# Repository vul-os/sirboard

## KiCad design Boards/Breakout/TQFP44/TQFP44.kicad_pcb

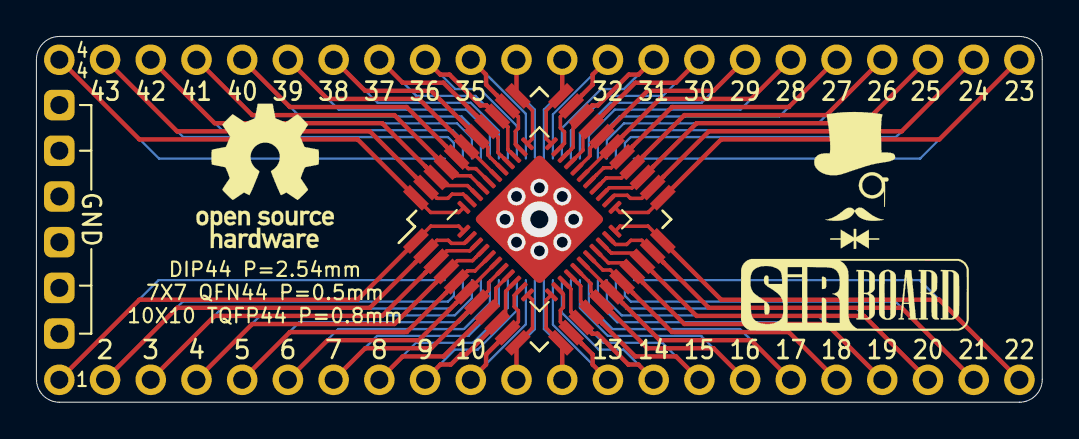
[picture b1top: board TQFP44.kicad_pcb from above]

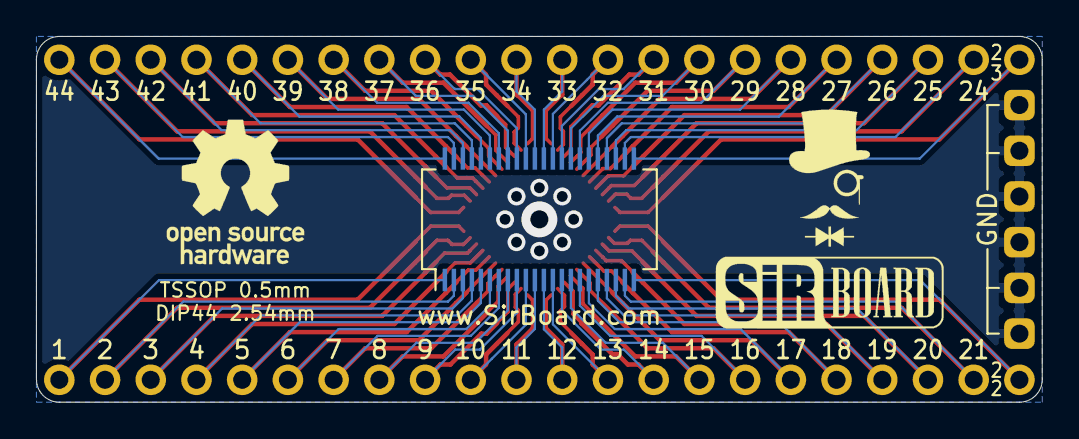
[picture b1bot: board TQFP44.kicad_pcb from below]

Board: 2 copper layers, 55.9 x 20.3 mm, 6 parts (2 on the bottom side), 45 nets.

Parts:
J1, J2: Conn_01x22; PinHeader_1x22_P2.54mm_Vertical
J3: Conn_02x22_Counter_Clockwise; TQFP-44_10x10mm_P0.8mm
J4: Conn_02x22_Counter_Clockwise; QFN-44-1EP_7x7mm_P0.5mm_EP5.15x5.15mm
J5: Conn_02x22_Counter_Clockwise; SSOP-44_5.3x12.8mm_P0.5mm
J6: Conn_01x06; PinHeader_1x06_P2.54mm_Vertical

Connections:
unnamed: J1.1, J3.44, J4.44, J5.23
unnamed: J1.2, J3.43, J4.43, J5.24
unnamed: J1.3, J3.42, J4.42, J5.25
unnamed: J1.4, J3.41, J4.41, J5.26
unnamed: J1.5, J3.40, J4.40, J5.27
unnamed: J1.6, J3.39, J4.39, J5.28
unnamed: J1.7, J3.38, J4.38, J5.29
unnamed: J1.8, J3.37, J4.37, J5.30
unnamed: J1.9, J3.36, J4.36, J5.31
unnamed: J1.10, J3.35, J4.35, J5.32
unnamed: J1.11, J3.34, J4.34, J5.33
unnamed: J1.12, J3.33, J4.33, J5.34
unnamed: J1.13, J3.32, J4.32, J5.35
unnamed: J1.14, J3.31, J4.31, J5.36
unnamed: J1.15, J3.30, J4.30, J5.37
unnamed: J1.16, J3.29, J4.29, J5.38
unnamed: J1.17, J3.28, J4.28, J5.39
unnamed: J1.18, J3.27, J4.27, J5.40
unnamed: J1.19, J3.26, J4.26, J5.41
unnamed: J1.20, J3.25, J4.25, J5.42
unnamed: J1.21, J3.24, J4.24, J5.43
unnamed: J1.22, J3.23, J4.23, J5.44
unnamed: J2.1, J3.1, J4.1, J5.22
unnamed: J2.2, J3.2, J4.2, J5.21
unnamed: J2.3, J3.3, J4.3, J5.20
unnamed: J2.4, J3.4, J4.4, J5.19
unnamed: J2.5, J3.5, J4.5, J5.18
unnamed: J2.6, J3.6, J4.6, J5.17
unnamed: J2.7, J3.7, J4.7, J5.16
unnamed: J2.8, J3.8, J4.8, J5.15
unnamed: J2.9, J3.9, J4.9, J5.14
unnamed: J2.10, J3.10, J4.10, J5.13
unnamed: J2.11, J3.11, J4.11, J5.12
unnamed: J2.12, J3.12, J4.12, J5.11
unnamed: J2.13, J3.13, J4.13, J5.10
unnamed: J2.14, J3.14, J4.14, J5.9
unnamed: J2.15, J3.15, J4.15, J5.8
unnamed: J2.16, J3.16, J4.16, J5.7
unnamed: J2.17, J3.17, J4.17, J5.6
unnamed: J2.18, J3.18, J4.18, J5.5
unnamed: J2.19, J3.19, J4.19, J5.4
unnamed: J2.20, J3.20, J4.20, J5.3
unnamed: J2.21, J3.21, J4.21, J5.2
unnamed: J2.22, J3.22, J4.22, J5.1
unnamed: J4.45, J6.1, J6.2, J6.3, J6.4, J6.5, J6.6

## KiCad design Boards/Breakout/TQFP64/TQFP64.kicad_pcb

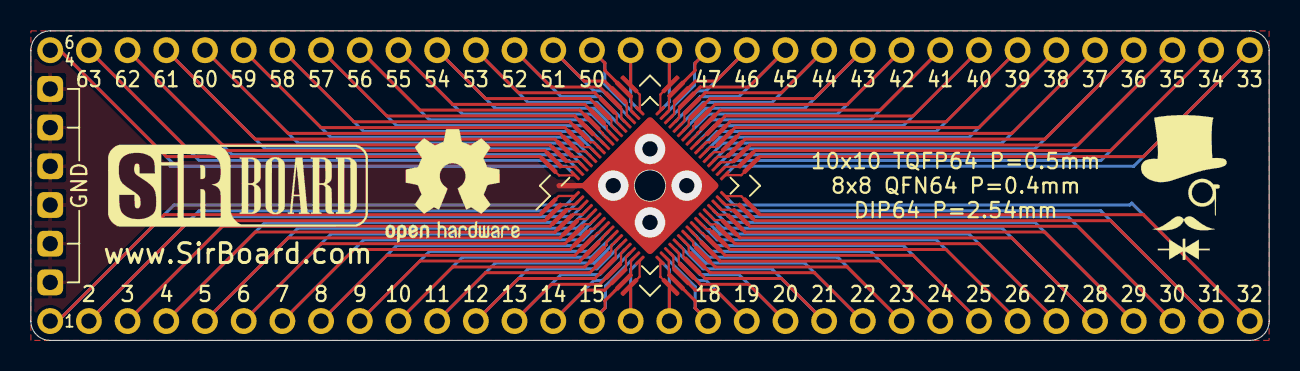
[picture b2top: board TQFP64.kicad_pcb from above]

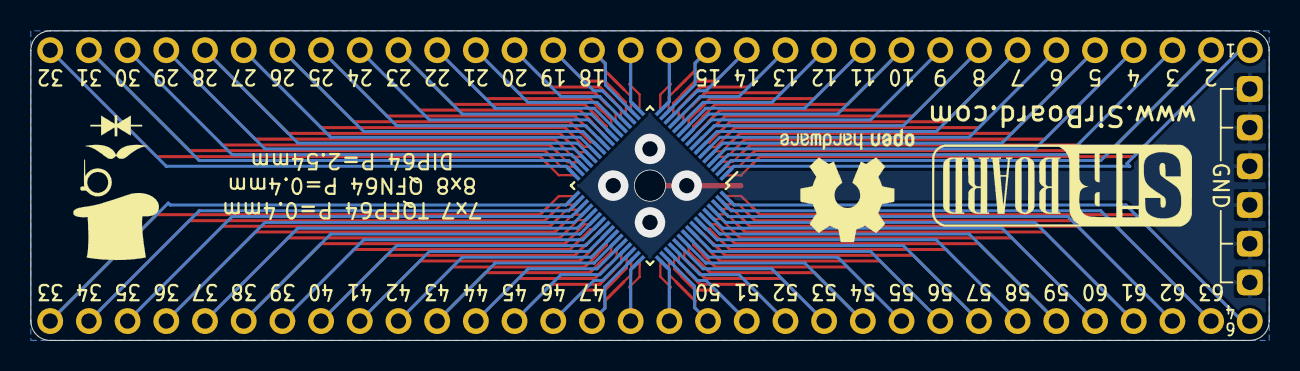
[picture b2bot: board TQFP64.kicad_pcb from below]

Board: 2 copper layers, 81.3 x 20.3 mm, 6 parts (4 on the bottom side), 65 nets.

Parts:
J1, J5: Conn_01x32; PinHeader_1x32_P2.54mm_Vertical
J2: Conn_02x32_Counter_Clockwise; TQFP-64_10x10mm_P0.5mm
J3: Conn_02x32_Counter_Clockwise; QFN-64-1EP_8x8mm_P0.4mm_EP6.5x6.5mm
J4: Conn_02x32_Counter_Clockwise; TQFP-64_7x7mm_P0.4mm
J6: Conn_01x06; PinHeader_1x06_P2.54mm_Vertical

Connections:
unnamed: J1.1, J2.1, J3.1, J4.64
unnamed: J1.2, J2.2, J3.2, J4.63
unnamed: J1.3, J2.3, J3.3, J4.62
unnamed: J1.4, J2.4, J3.4, J4.61
unnamed: J1.5, J2.5, J3.5, J4.60
unnamed: J1.6, J2.6, J3.6, J4.59
unnamed: J1.7, J2.7, J3.7, J4.58
unnamed: J1.8, J2.8, J3.8, J4.57
unnamed: J1.9, J2.9, J3.9, J4.56
unnamed: J1.10, J2.10, J3.10, J4.55
unnamed: J1.11, J2.11, J3.11, J4.54
unnamed: J1.12, J2.12, J3.12, J4.53
unnamed: J1.13, J2.13, J3.13, J4.52
unnamed: J1.14, J2.14, J3.14, J4.51
unnamed: J1.15, J2.15, J3.15, J4.50
unnamed: J1.16, J2.16, J3.16, J4.49
unnamed: J1.17, J2.17, J3.17, J4.48
unnamed: J1.18, J2.18, J3.18, J4.47
unnamed: J1.19, J2.19, J3.19, J4.46
unnamed: J1.20, J2.20, J3.20, J4.45
unnamed: J1.21, J2.21, J3.21, J4.44
unnamed: J1.22, J2.22, J3.22, J4.43
unnamed: J1.23, J2.23, J3.23, J4.42
unnamed: J1.24, J2.24, J3.24, J4.41
unnamed: J1.25, J2.25, J3.25, J4.40
unnamed: J1.26, J2.26, J3.26, J4.39
unnamed: J1.27, J2.27, J3.27, J4.38
unnamed: J1.28, J2.28, J3.28, J4.37
unnamed: J1.29, J2.29, J3.29, J4.36
unnamed: J1.30, J2.30, J3.30, J4.35
unnamed: J1.31, J2.31, J3.31, J4.34
unnamed: J1.32, J2.32, J3.32, J4.33
unnamed: J2.33, J3.33, J4.32, J5.32
unnamed: J2.34, J3.34, J4.31, J5.31
unnamed: J2.35, J3.35, J4.30, J5.30
unnamed: J2.36, J3.36, J4.29, J5.29
unnamed: J2.37, J3.37, J4.28, J5.28
unnamed: J2.38, J3.38, J4.27, J5.27
unnamed: J2.39, J3.39, J4.26, J5.26
unnamed: J2.40, J3.40, J4.25, J5.25
unnamed: J2.41, J3.41, J4.24, J5.24
unnamed: J2.42, J3.42, J4.23, J5.23
unnamed: J2.43, J3.43, J4.22, J5.22
unnamed: J2.44, J3.44, J4.21, J5.21
unnamed: J2.45, J3.45, J4.20, J5.20
unnamed: J2.46, J3.46, J4.19, J5.19
unnamed: J2.47, J3.47, J4.18, J5.18
unnamed: J2.48, J3.48, J4.17, J5.17
unnamed: J2.49, J3.49, J4.16, J5.16
unnamed: J2.50, J3.50, J4.15, J5.15
unnamed: J2.51, J3.51, J4.14, J5.14
unnamed: J2.52, J3.52, J4.13, J5.13
unnamed: J2.53, J3.53, J4.12, J5.12
unnamed: J2.54, J3.54, J4.11, J5.11
unnamed: J2.55, J3.55, J4.10, J5.10
unnamed: J2.56, J3.56, J4.9, J5.9
unnamed: J2.57, J3.57, J4.8, J5.8
unnamed: J2.58, J3.58, J4.7, J5.7
unnamed: J2.59, J3.59, J4.6, J5.6
unnamed: J2.60, J3.60, J4.5, J5.5
unnamed: J2.61, J3.61, J4.4, J5.4
unnamed: J2.62, J3.62, J4.3, J5.3
unnamed: J2.63, J3.63, J4.2, J5.2
unnamed: J2.64, J3.64, J4.1, J5.1
unnamed: J3.65, J6.1, J6.2, J6.3, J6.4, J6.5, J6.6

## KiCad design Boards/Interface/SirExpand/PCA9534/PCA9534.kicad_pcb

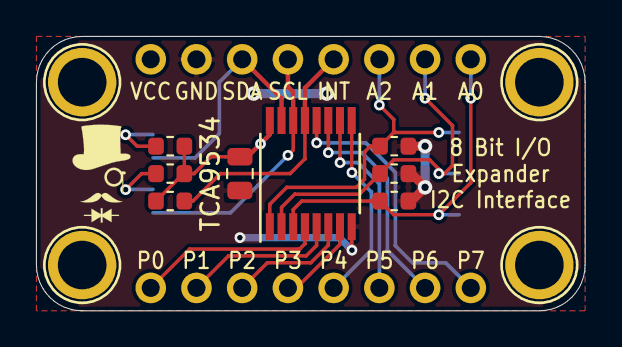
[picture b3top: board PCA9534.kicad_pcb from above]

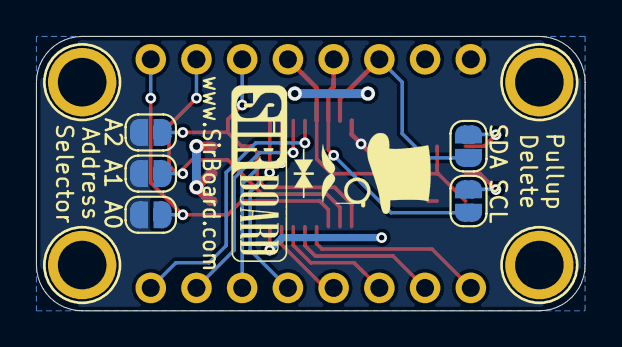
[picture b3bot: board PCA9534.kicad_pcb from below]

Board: 2 copper layers, 30.5 x 15.2 mm, 19 parts (5 on the bottom side), 18 nets.

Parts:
A0, A1, A2: SolderJumper_2_Open; SolderJumper-2_P1.3mm_Open_RoundedPad1.0x1.5mm
C1: 10uF; C_0805_2012Metric
H1, H2, H3, H4: MountingHole; MountingHole_M2.5_SirBoard
J1, J2: Conn_01x08; PinHeader_1x08_P2.54mm_Vertical
R1, R2, R3, R4, R5, R6: 10K; R_0603_1608Metric
SCL: SolderJumper_2_Open; SolderJumper-2_P1.3mm_Open_RoundedPad1.0x1.5mm
SDA: SolderJumper_2_Open; SolderJumper-2_P1.3mm_Open_RoundedPad1.0x1.5mm
TCA9534: TCA9534; TSSOP-16_4.4x5mm_P0.65mm

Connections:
A0: A0.1, J1.8, R1.1, TCA9534.3
A1: A1.1, J1.7, R4.1, TCA9534.2
A2: A2.1, J1.6, R5.1, TCA9534.1
GND: C1.2, J1.2, R1.2, R4.2, R5.2, TCA9534.8
INT: J1.5, R6.2, TCA9534.13
unnamed: R2.2, SCL.1
unnamed: R3.2, SDA.1
P0: J2.8, TCA9534.4
P1: J2.7, TCA9534.5
P2: J2.6, TCA9534.6
P3: J2.5, TCA9534.7
P4: J2.4, TCA9534.9
P5: J2.3, TCA9534.10
P6: J2.2, TCA9534.11
P7: J2.1, TCA9534.12
SCL: J1.4, SCL.2, TCA9534.14
SDA: J1.3, SDA.2, TCA9534.15
VCC: A0.2, A1.2, A2.2, C1.1, J1.1, R2.1, R3.1, R6.1, TCA9534.16

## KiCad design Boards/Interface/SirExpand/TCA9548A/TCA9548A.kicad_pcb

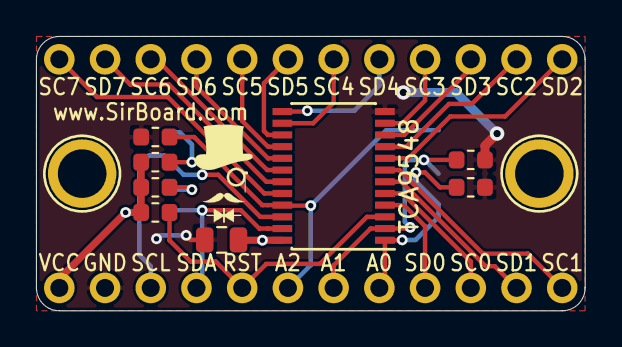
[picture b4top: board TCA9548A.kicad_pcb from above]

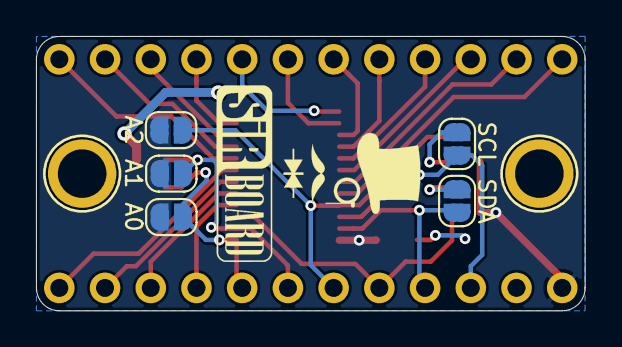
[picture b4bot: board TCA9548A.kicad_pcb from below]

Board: 2 copper layers, 30.5 x 15.2 mm, 15 parts (5 on the bottom side), 26 nets.

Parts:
A0, A1, A2: SolderJumper_2_Open; SolderJumper-2_P1.3mm_Open_RoundedPad1.0x1.5mm
C1: 10uF; C_0805_2012Metric
J1, J2: Conn_01x12; PinHeader_1x12_P2.54mm_Vertical
R1, R2, R3, R4, R5, R6: 10K; R_0603_1608Metric
SCL: SolderJumper_2_Open; SolderJumper-2_P1.3mm_Open_RoundedPad1.0x1.5mm
SDA: SolderJumper_2_Open; SolderJumper-2_P1.3mm_Open_RoundedPad1.0x1.5mm
TCA9548: TCA9548APWR; TSSOP-24_4.4x7.8mm_P0.65mm

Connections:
A0: A0.1, J1.8, R1.1, TCA9548.1
A1: A1.1, J1.7, R4.1, TCA9548.2
A2: A2.1, J1.6, R5.1, TCA9548.21
GND: C1.2, J1.2, R1.2, R4.2, R5.2, TCA9548.12
unnamed: R2.2, SCL.1
unnamed: R3.2, SDA.1
RST: J1.5, R6.2, TCA9548.3
SCL: J1.3, SCL.2, TCA9548.22
SCL0: J1.10, TCA9548.5
SCL1: J1.12, TCA9548.7
SCL2: J2.11, TCA9548.9
SCL3: J2.9, TCA9548.11
SCL4: J2.7, TCA9548.14
SCL5: J2.5, TCA9548.16
SCL6: J2.3, TCA9548.18
SCL7: J2.1, TCA9548.20
SDA: J1.4, SDA.2, TCA9548.23
SDA0: J1.9, TCA9548.4
SDA1: J1.11, TCA9548.6
SDA2: J2.12, TCA9548.8
SDA3: J2.10, TCA9548.10
SDA4: J2.8, TCA9548.13
SDA5: J2.6, TCA9548.15
SDA6: J2.4, TCA9548.17
SDA7: J2.2, TCA9548.19
VCC: A0.2, A1.2, A2.2, C1.1, J1.1, R2.1, R3.1, R6.1, TCA9548.24

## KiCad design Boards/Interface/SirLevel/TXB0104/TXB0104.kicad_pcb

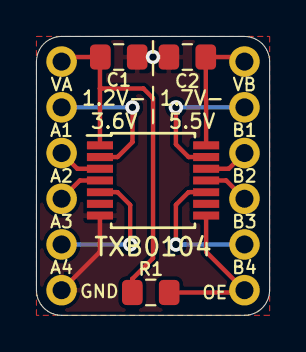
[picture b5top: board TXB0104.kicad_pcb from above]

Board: 2 copper layers, 13.0 x 15.5 mm, 6 parts (0 on the bottom side), 12 nets.

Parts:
C1, C2: 100nF; C_0805_2012Metric_Pad1.15x1.40mm_HandSolder
J1, J2: Conn_01x06; PinHeader_1x06_P2.54mm_Vertical
R1: 10k; R_0805_2012Metric_Pad1.15x1.40mm_HandSolder
TXB0104: TXB0104PW; TSSOP-14_4.4x5mm_P0.65mm

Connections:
/A1: J1.2, TXB0104.2
/A2: J1.3, TXB0104.3
/A3: J1.4, TXB0104.4
/A4: J1.5, TXB0104.5
/B1: J2.2, TXB0104.13
/B2: J2.3, TXB0104.12
/B3: J2.4, TXB0104.11
/B4: J2.5, TXB0104.10
/GND: C1.1, C2.1, J1.6, TXB0104.7
/OE: J2.6, R1.2, TXB0104.8
/VHI: C2.2, J2.1, TXB0104.14
/VLOW: C1.2, J1.1, R1.1, TXB0104.1

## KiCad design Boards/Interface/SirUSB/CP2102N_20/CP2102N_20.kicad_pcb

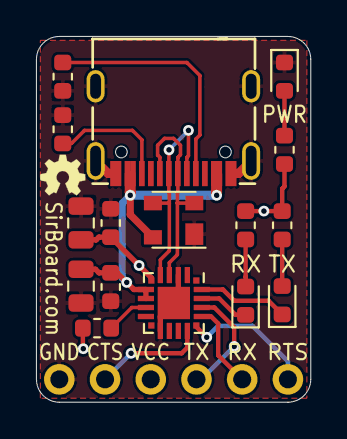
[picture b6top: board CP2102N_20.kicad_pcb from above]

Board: 2 copper layers, 15.2 x 20.3 mm, 17 parts (0 on the bottom side), 17 nets.

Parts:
C1, C4: 100nF; C_0603_1608Metric
C2, C5: 4.7uF; C_0805_2012Metric
D1: PRTR5V0U2X; SOT-143
J1: Conn_01x06; PinHeader_1x06_P2.54mm_Horizontal
P1: USB_C_Plug_USB2.0; USB_C
PWR: RED; LED_0603_1608Metric
R1, R3, R5, R6: 1K; R_0603_1608Metric
R2, R4: 5K1; R_0603_1608Metric
RX: GREEN; LED_0603_1608Metric
TX: GREEN; LED_0603_1608Metric
U1: CP2102N-A01-GQFN20; SiliconLabs_QFN-20-1EP_3x3mm_P0.5mm

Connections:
/CC1: P1.A5, R4.1
/CC2: P1.B5, R2.1
CTS: J1.5, U1.15
GND: C1.2, C2.2, C4.2, C5.2, D1.1, J1.6, P1.A1, P1.A12, P1.B1, P1.B12, P1.S1, PWR.1, R2.2, R4.2, U1.3, U1.12, U1.21
GPIO.2: TX.1, U1.20
GPIO.3: RX.1, U1.19
unnamed: PWR.2, R1.2
unnamed: R3.2, TX.2
unnamed: R5.2, RX.2
RST: R6.2, U1.9
RTS: J1.1, U1.16
RX: J1.2, U1.17
TX: J1.3, U1.18
VBUS: C1.1, C2.1, D1.4, P1.A4, P1.A9, P1.B4, P1.B9, U1.7, U1.8
VDD: C4.1, C5.1, J1.4, R1.1, R3.1, R5.1, R6.1, U1.6
uD+: D1.2, P1.A6, P1.B6, U1.4
uD-: D1.3, P1.A7, P1.B7, U1.5

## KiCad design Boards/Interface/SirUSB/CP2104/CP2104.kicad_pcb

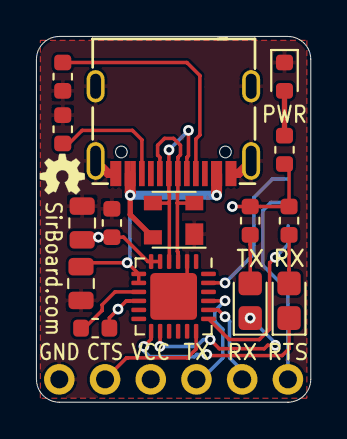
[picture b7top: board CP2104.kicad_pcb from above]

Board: 2 copper layers, 15.2 x 20.3 mm, 17 parts (1 on the bottom side), 19 nets.

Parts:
C1: 1uF; C_0805_2012Metric
C4: 100nF; C_0603_1608Metric
C5: 4.7uF; C_0805_2012Metric
D1: PRTR5V0U2X; SOT-143
J1: Conn_01x06; PinHeader_1x06_P2.54mm_Horizontal
JP2: SolderJumper_3_Open; SolderJumper-3_P1.3mm_Open_RoundedPad1.0x1.5mm
P1: USB_C_Plug_USB2.0; USB_C
PWR: RED; LED_0603_1608Metric
R1, R3, R5: 1K; R_0603_1608Metric
R2, R4: 5K1; R_0603_1608Metric
R6: 4K7; R_0603_1608Metric
RX: GREEN; LED_0805_2012Metric_Castellated
TX: GREEN; LED_0805_2012Metric_Castellated
U1: CP2104; QFN-24-1EP_4x4mm_P0.5mm_EP2.6x2.6mm

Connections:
/CC1: P1.A5, R4.1
/CC2: P1.B5, R2.1
CTS: J1.5, U1.18
DTR: JP2.3, U1.23
DTR_RTS: J1.1, JP2.2
GND: C1.2, C4.2, C5.2, D1.1, J1.6, P1.A1, P1.A12, P1.B1, P1.B12, P1.S1, PWR.1, R2.2, R4.2, U1.2, U1.25
GPIO.0: TX.1, U1.14
GPIO.1: RX.1, U1.13
unnamed: PWR.2, R1.2
unnamed: R3.2, TX.2
unnamed: R5.2, RX.2
RST: R6.2, U1.9
RTS: JP2.1, U1.19
RX: J1.2, U1.20
TX: J1.3, U1.21
VBUS: C1.1, D1.4, P1.A4, P1.A9, P1.B4, P1.B9, U1.7, U1.8
VDD: C4.1, C5.1, J1.4, R1.1, R3.1, R5.1, R6.1, U1.5, U1.6, U1.10
uD+: D1.2, P1.A6, P1.B6, U1.3
uD-: D1.3, P1.A7, P1.B7, U1.4

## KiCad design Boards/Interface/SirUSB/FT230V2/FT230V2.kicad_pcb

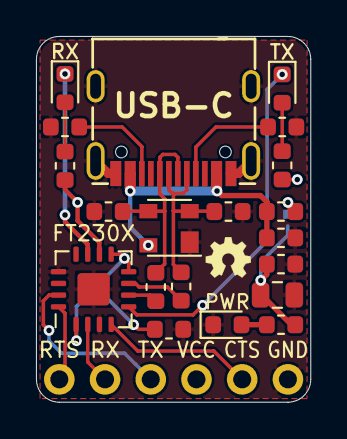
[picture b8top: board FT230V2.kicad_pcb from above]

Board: 2 copper layers, 15.2 x 20.3 mm, 22 parts (1 on the bottom side), 20 nets.

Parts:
C1: 10nF; C_0603_1608Metric
C2, C3: 47pF; C_0603_1608Metric
C4, C6: 100nF; C_0603_1608Metric
C5: 4.7uF; C_0805_2012Metric
D1: PRTR5V0U2X; SOT-143
FB1: 40E@100MHz; L_0603_1608Metric
J1: Conn_01x06; PinHeader_1x06_P2.54mm_Horizontal
JP1: SolderJumper_2_Open; SolderJumper-2_P1.3mm_Bridged_RoundedPad1.0x1.5mm
PWR: RED; LED_0603_1608Metric
R1, R2: 27e; R_0603_1608Metric
R3, R4, R5: 1k; R_0603_1608Metric
R6, R7: 5k1; R_0603_1608Metric
RX: GREEN; LED_0603_1608Metric
TX: GREEN; LED_0603_1608Metric
U1: FT230XQ; QFN-16-1EP_4x4mm_P0.65mm_EP2.1x2.1mm
USB-C: USB_C_Plug_USB2.0; USB_C

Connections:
CBUS1: RX.1, U1.11
CBUS2: TX.1, U1.5
CTS: J1.2, U1.4
D+: C2.1, D1.3, R2.2, USB-C.A6, USB-C.B6
D-: C3.1, D1.2, R1.1, USB-C.A7, USB-C.B7
GND: C1.2, C2.2, C3.2, C4.2, C5.2, C6.2, D1.1, J1.1, PWR.1, R6.2, R7.2, U1.3, U1.13, U1.17, USB-C.A1, USB-C.A12, USB-C.B1, USB-C.B12, USB-C.S1
unnamed: C6.1, U1.1, U1.8, U1.9
unnamed: FB1.1, JP1.1
unnamed: R7.1, USB-C.A5
unnamed: R6.1, USB-C.B5
unnamed: PWR.2, R4.2
unnamed: R3.2, TX.2
unnamed: R5.2, RX.2
RTS: J1.6, U1.16
RX: J1.5, U1.2
TX: J1.4, U1.15
VCC: C4.1, C5.1, J1.3, JP1.2, R3.1, R4.1, R5.1, U1.10
VUSB: C1.1, D1.4, FB1.2, USB-C.A4, USB-C.A9, USB-C.B4, USB-C.B9
uD+: R2.1, U1.6
uD-: R1.2, U1.7
